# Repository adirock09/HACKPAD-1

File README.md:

# HACKPAD-1<br>
<br>

My custom hack pad with 4 Keys made for general shortcuts. It is based on SeedStudio XIAO RP2040.<br>

#  BOM<br>
1 x XIAO RP2040<br>
 4 x MX-Style switches<br>
 4 x Blank DSA keycaps<br>
 4 x M3x16mm screws<br>
 4 x M3x5mx4mm heatset inserts<br>

 # Schematic<br>

#  PCB<br>

#  Final Look<br>

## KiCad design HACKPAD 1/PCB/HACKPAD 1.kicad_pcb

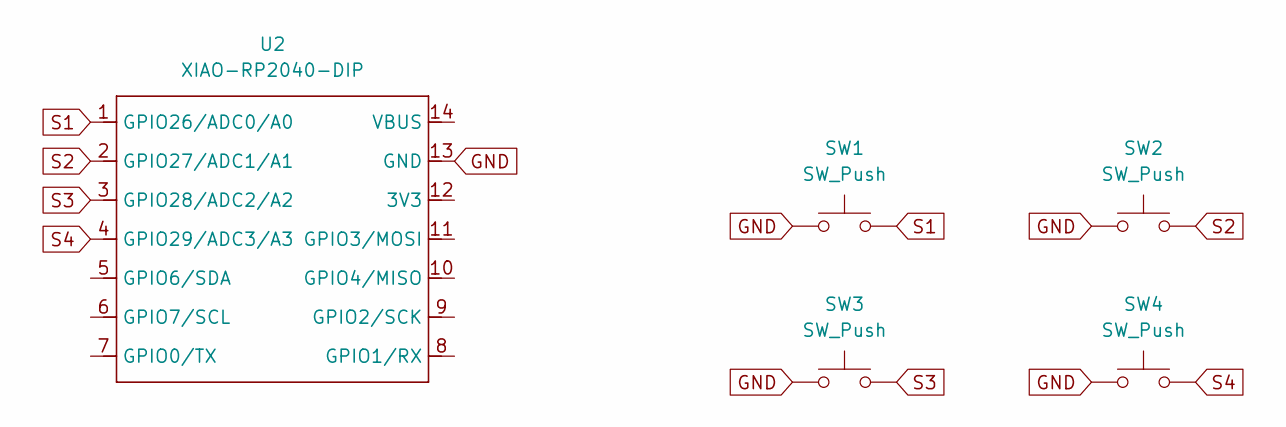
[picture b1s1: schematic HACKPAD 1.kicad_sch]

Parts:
SW1, SW2, SW3, SW4: SW_Push; SW_Cherry_MX_1.00u_PCB
U2: XIAO-RP2040-DIP

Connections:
GND: SW1.1, SW2.1, SW3.1, SW4.1, U2.13 (GND)
S1: SW1.2, U2.1 (GPIO26/ADC0/A0)
S2: SW2.2, U2.2 (GPIO27/ADC1/A1)
S3: SW3.2, U2.3 (GPIO28/ADC2/A2)
S4: SW4.2, U2.4 (GPIO29/ADC3/A3)

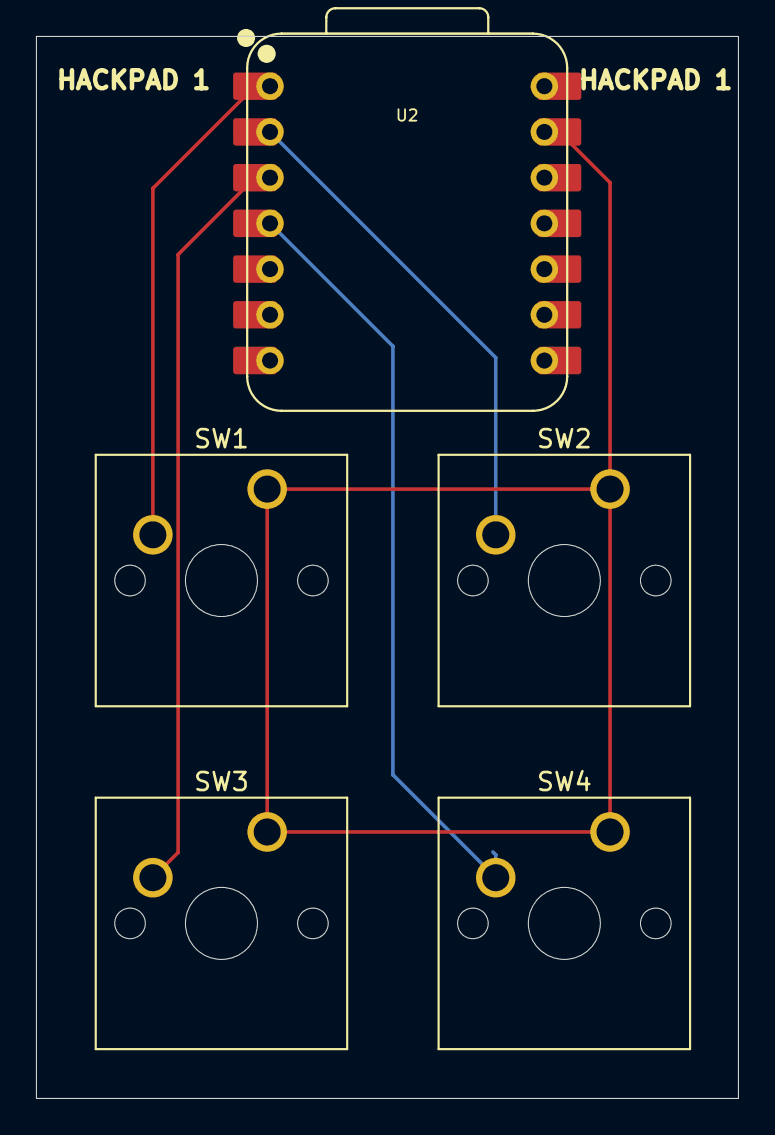
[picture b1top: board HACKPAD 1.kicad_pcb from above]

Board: 2 copper layers, 39.0 x 59.0 mm, 5 parts (0 on the bottom side), 5 nets.
